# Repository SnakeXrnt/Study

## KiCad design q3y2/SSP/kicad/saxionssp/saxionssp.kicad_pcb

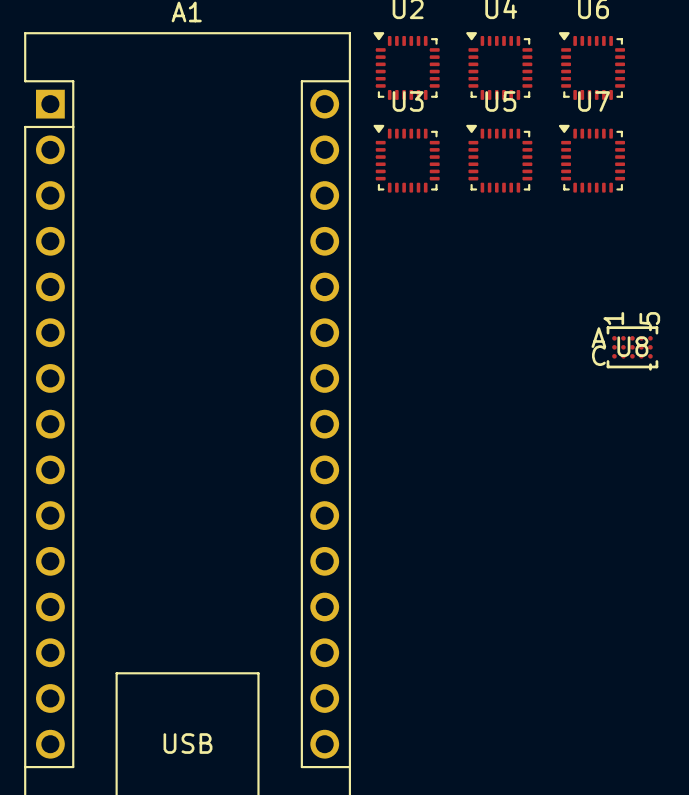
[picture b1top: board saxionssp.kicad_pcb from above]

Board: 2 copper layers, 8 parts (0 on the bottom side), 3 nets, no tracks yet.

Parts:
A1: Arduino_Nano_ESP32; Arduino_Nano
U2, U3, U4, U5, U6, U7: MPU-9250; InvenSense_QFN-24_3x3mm_P0.4mm
U8: MAX17335X22+T; 21-100433_W151J2&plus_1_ADI

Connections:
/SCL - BMS: A1.24 (SCL/A5), U8.B5 (SCL)
/SDA - BMS: A1.23 (SDA/A4), U8.C5 (SDA)
unnamed: A1.4 (GND), A1.29 (GND)

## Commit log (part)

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2025-11-10 Initial init corrected
    y2q2 included
2025-11-10 test 2
2025-11-14 APC week 1 done, ID week 1 done
2025-11-14 CAS week 1 in progress
2025-11-14 ID week 1 done
2025-11-15 CAS assignment 4 done
2025-11-20 APC WEEK 2 done
2025-11-24 week1 CAS done
2025-11-24 ID week1 done
2025-11-25 APC WEEK3 SEMI DONE
2025-11-25 week1 and 2 apc submitted
2025-11-26 working on APC
2025-11-28 push weekend week3
2025-12-10 hasnt commited since idunnowehn
2025-12-14 ID week 34 done
2025-12-25 winter break push 1
    winter break push the first time
2026-01-03 Add new file idontknowhat
2026-01-03 WEEK6 ID DONE
    DOING APC NEXT
2026-01-07 APC W5 done
2026-01-10 studyDSA
2026-01-22 22012026
2026-01-26 revisiting python
2026-02-04 chore : new CAS riscv remake
2026-03-09 first commit in mac
2026-03-26 Big push from mac
2026-03-28 schematics ssp done
2026-03-31 add freertosexample
2026-04-04 add ssp
2026-04-06 add connection benchmark int
2026-04-13 feat: add pomodoro timer with TUI interface
2026-05-10 feat : adding oled and encoder func in macropad
2026-05-11 feat : broking pico
2026-05-18 bigg push
2026-06-01 BLE working
2026-06-01 chrore : BLE done, making lib next
2026-06-06 chore : ble-keyboard-ttgo done
2026-06-18 RTOS logbook q4 a2 in the making
2026-06-19 Logbook RTOS in the making
2026-06-19 Logbook in the making, switch back to rog
2026-06-28 Advanced Microcontroller logbook done
